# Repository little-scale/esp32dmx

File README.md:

# esp32dmx
esp32dmx

A simple ESP32 to DMX interface using a MAX485 chip which transmits on digital pin 14 (ESP32 port 1). 

Note the PCB uses ESP32-DEVKIT-V1 as the ESP32 part and a DIL version of the MAX485 chip.

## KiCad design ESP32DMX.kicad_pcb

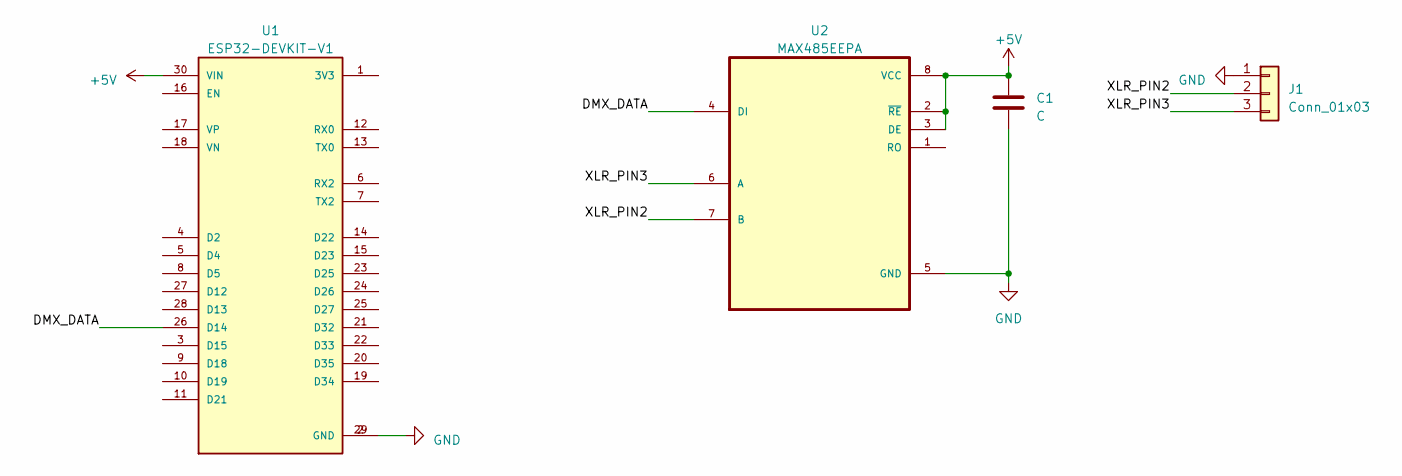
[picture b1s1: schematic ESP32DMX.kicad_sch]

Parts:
C1: C; C_Disc_D5.0mm_W2.5mm_P5.00mm
J1: Conn_01x03; PinSocket_1x03_P2.54mm_Vertical
U1: ESP32-DEVKIT-V1; MODULE_ESP32_DEVKIT_V1; PARTREV N/A
U2: MAX485EEPA; DIP794W47P254L991H457Q8

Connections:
+5V: C1.1, U1.30 (VIN), U2.2 (~RE), U2.3 (DE), U2.8 (VCC)
/DMX_DATA: U1.26 (D14), U2.4 (DI)
/XLR_PIN2: J1.2, U2.7 (B)
/XLR_PIN3: J1.3, U2.6 (A)
GND: C1.2, J1.1, U1.2 (GND), U1.29 (GND), U2.5 (GND)

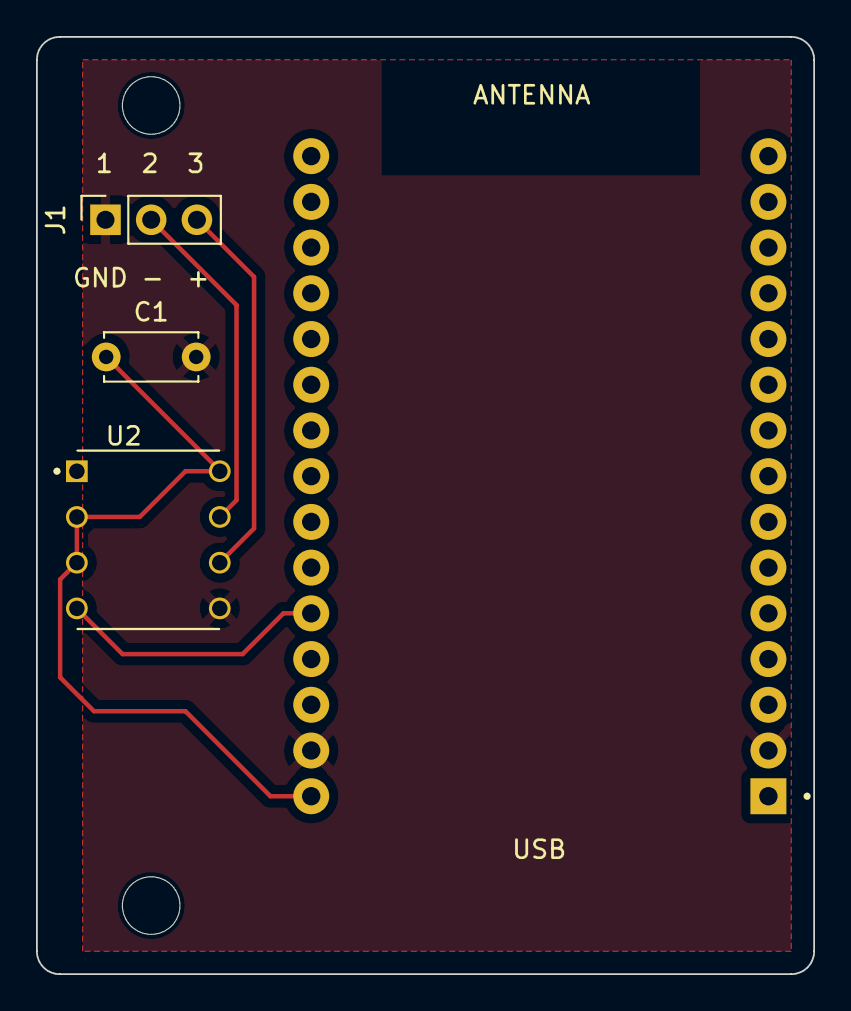
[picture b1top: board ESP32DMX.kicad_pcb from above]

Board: 2 copper layers, 43.2 x 52.1 mm, 4 parts (0 on the bottom side), 5 nets.
